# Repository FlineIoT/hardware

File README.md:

# breakoutboard

This is the first prototype design with breakouts boards

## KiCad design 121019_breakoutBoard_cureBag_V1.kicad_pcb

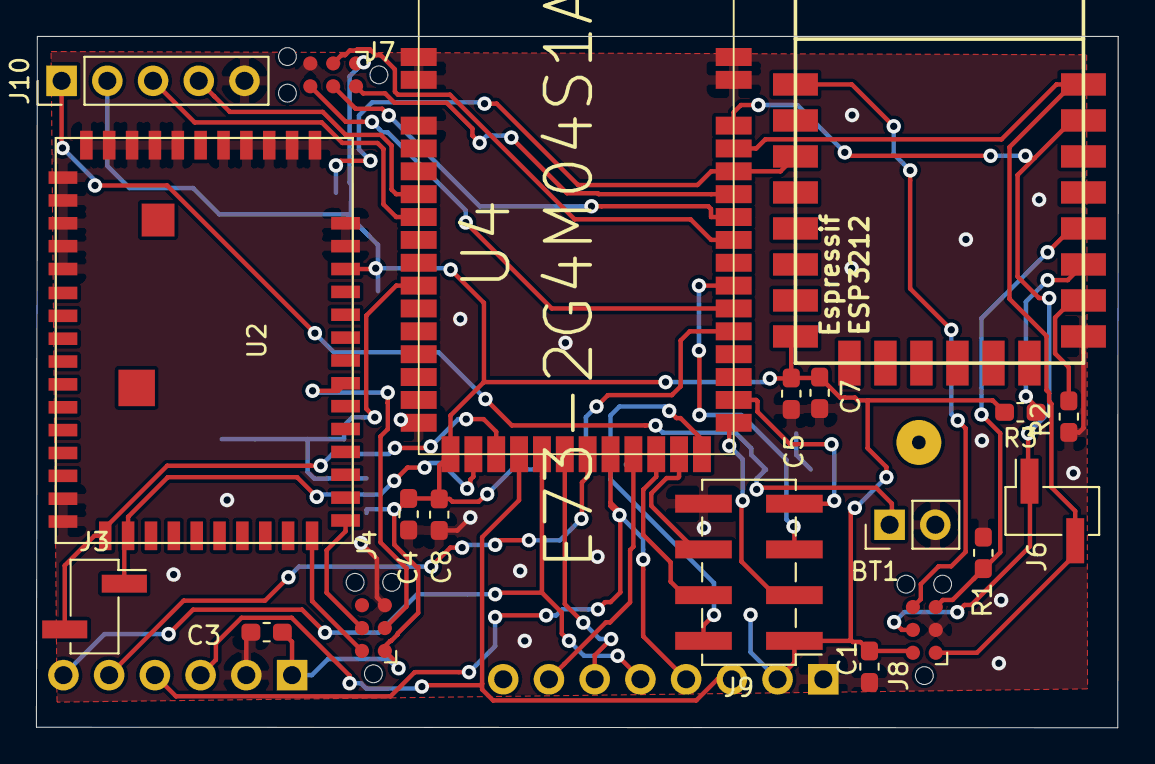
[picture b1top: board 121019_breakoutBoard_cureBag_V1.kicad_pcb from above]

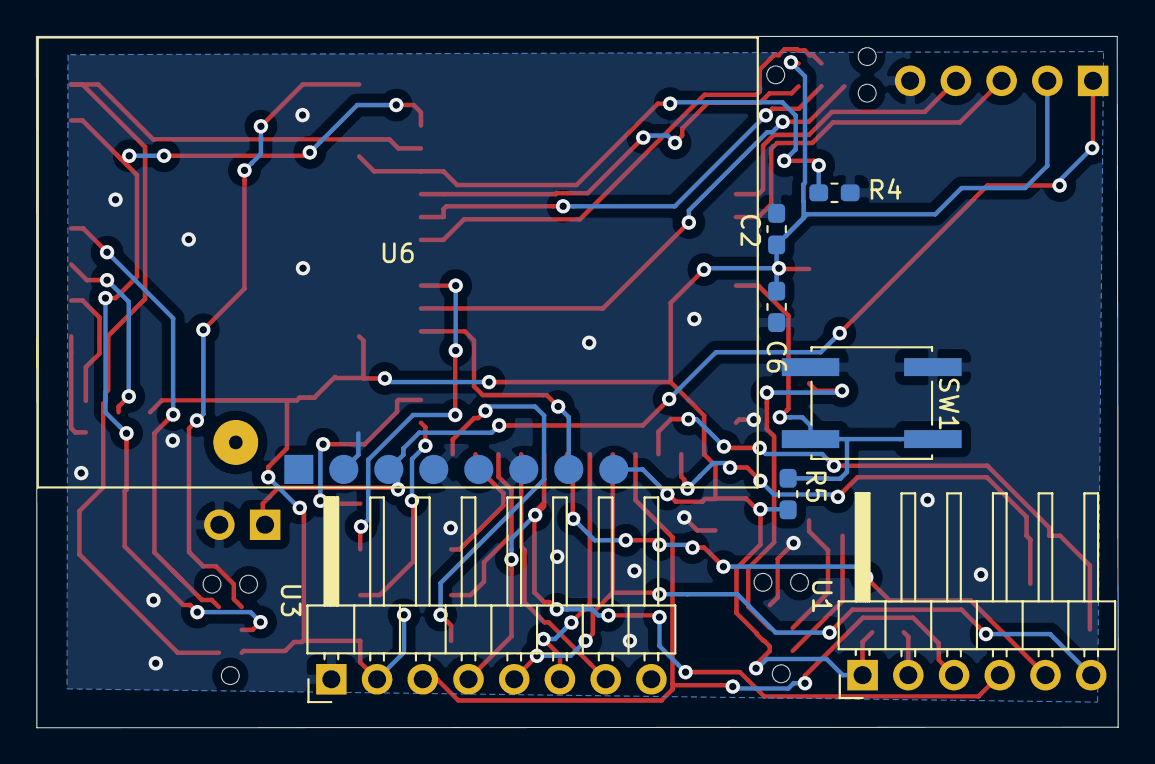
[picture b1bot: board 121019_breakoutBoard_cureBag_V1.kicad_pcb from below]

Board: 2 copper layers, 60.1 x 38.4 mm, 28 parts (8 on the bottom side), 35 nets.

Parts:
BT1: Battery_Cell; PinHeader_1x02_P2.54mm_Vertical
C1, C2, C3, C4, C5: 100nF; C_0603_1608Metric_Pad1.05x0.95mm_HandSolder
C6, C7, C8: 2.2µF; C_0603_1608Metric_Pad1.05x0.95mm_HandSolder
J3: UART_WSG_DEBUG; PinHeader_1x02_P2.54mm_Vertical_SMD_Pin1Right
J4: JTAG_SIGFOX; Tag-Connect_TC2030-IDC-NL_2x03_P1.27mm_Vertical
J6: UART_ESP_DEBUG; PinHeader_1x02_P2.54mm_Vertical_SMD_Pin1Right
J7: JTAG_NRF; Tag-Connect_TC2030-IDC-NL_2x03_P1.27mm_Vertical
J8: JTAG_ESP; Tag-Connect_TC2030-IDC-NL_2x03_P1.27mm_Vertical
J9: GPIOs; PinHeader_2x04_P2.54mm_Vertical_SMD
J10: LED; PinHeader_1x05_P2.54mm_Vertical
R1, R2, R3, R4, R5: 100k; R_0603_1608Metric_Pad1.05x0.95mm_HandSolder
SW1: SW_Push; SW_SPST_EVQQ2
U1: GY-BME280; PinHeader_1x06_P2.54mm_Horizontal
U2: WSG303S; Wsg303s
U3: LIS2DS12; PinHeader_1x08_P2.54mm_Horizontal
U4: E73-2G4M04S1A; E73-2G4M04S-E73_2G4M04S
U5: ESP-12F; ESP3212
U6: SpeedRiderPlus; Lipo_Rider_plus

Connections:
+3V3: C1.2, C2.2, C3.2, C4.2, C5.2, C6.1, C7.1, C8.1, J4.1, J7.1, J8.2, J9.1, J10.2, R3.2, R5.1, U1.1, U2.38, U3.2, U4.17, U5.8, U6.8
/En_Bat: U4.33, U6.7
/P0.19: J9.5, U4.35
/RESET_ESP: J8.6, U5.1
/UART_RX_E73_TX_WSG: J3.2, U2.17, U4.19
/UART_TX_E73_RX_WSG: J3.1, U2.18, U4.18
/Vbat: BT1.1, J10.1, U6.3
GND: BT1.2, C1.1, C2.1, C3.1, C4.1, C5.1, C6.2, C7.2, C8.2, J4.5, J7.5, J8.3, J9.8, J10.5, R1.2, R2.2, R4.2, SW1.1, U1.2, U2.1, U2.2, U2.3, U2.4, U2.5, U2.15, U2.16, U2.39, U2.40, U2.41, U2.42, U2.43, U2.44, U2.45, U2.47, U2.48, U2.49, U2.50, U2.51, U3.1, U4.1, U4.2, U4.3, U4.16, U4.43, U4.44, U5.15, U6.2, U6.4, U6.6
unnamed: J4.2, U2.26
unnamed: J4.3, U2.33
unnamed: J4.4, U2.27
unnamed: J6.1, J8.4, U4.42, U5.21
unnamed: J6.2, J8.1, U4.41, U5.22
unnamed: J7.2, U4.39
unnamed: J7.3, U4.37
unnamed: J7.4, U4.38
unnamed: J7.6, U4.34
unnamed: J8.5, R1.1, U5.18
unnamed: J9.2, U4.28
unnamed: J9.3, U4.29
unnamed: J9.4, U4.26
unnamed: J9.6, U4.27
unnamed: J9.7, U4.30
unnamed: J10.3, U4.7
unnamed: J10.4, U4.6
unnamed: R2.1, U5.16
unnamed: R3.1, U5.17
unnamed: R4.1, U4.40, U5.3
unnamed: R5.2, SW1.2, U4.10
unnamed: U1.3, U3.3, U4.20
unnamed: U1.4, U3.4, U4.24
unnamed: U1.5, U4.23
unnamed: U1.6, U3.5, U4.21
unnamed: U3.6, U4.22
unnamed: U3.7, U4.25

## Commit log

2019-11-04 init(repo): add all file of V0 Breakoutboard
2019-11-18 fix(lipoRider): change lipo rider footprint
